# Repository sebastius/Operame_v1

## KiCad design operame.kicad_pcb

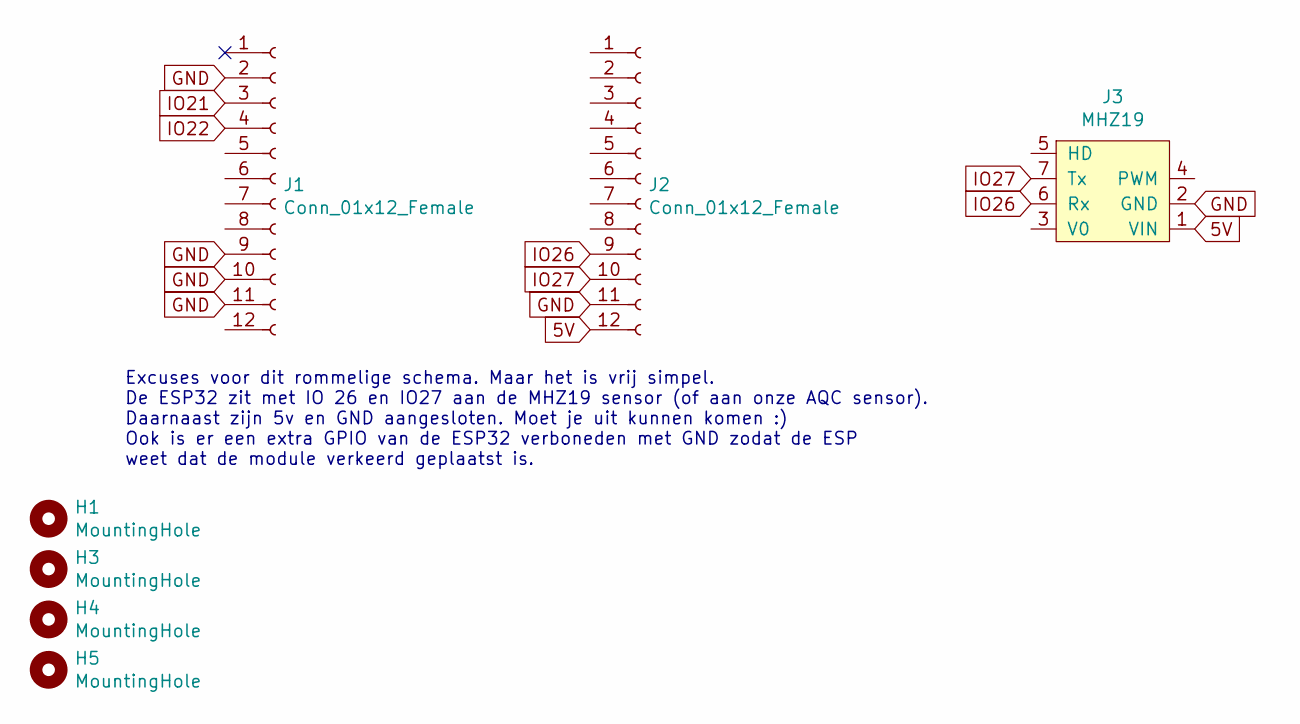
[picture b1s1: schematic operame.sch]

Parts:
H1, H3, H4, H5: MountingHole; MountingHole_3.2mm_M3
J1, J2: Conn_01x12_Female; PinSocket_1x12_P2.54mm_Vertical_SMD_Pin1Left
J3: MHZ19; Sensor_MH-Z19

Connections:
5V: J2.12, J3.1 (VIN)
GND: J1.2, J1.9, J1.10, J1.11, J2.11, J3.2 (GND)
IO21: J1.3
IO22: J1.4
IO26: J2.9, J3.6 (Rx)
IO27: J2.10, J3.7 (Tx)

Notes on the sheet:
Excuses voor dit rommelige schema. Maar het is vrij simpel. De ESP32 zit met IO 26 en IO27 aan de MHZ19 sensor (of aan onze AQC sensor). Daarnaast zijn 5v en GND aangesloten. Moet je uit kunnen komen :) Ook is er een extra GPIO van de ESP32 verboneden met GND zodat de ESP weet dat de module verkeer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

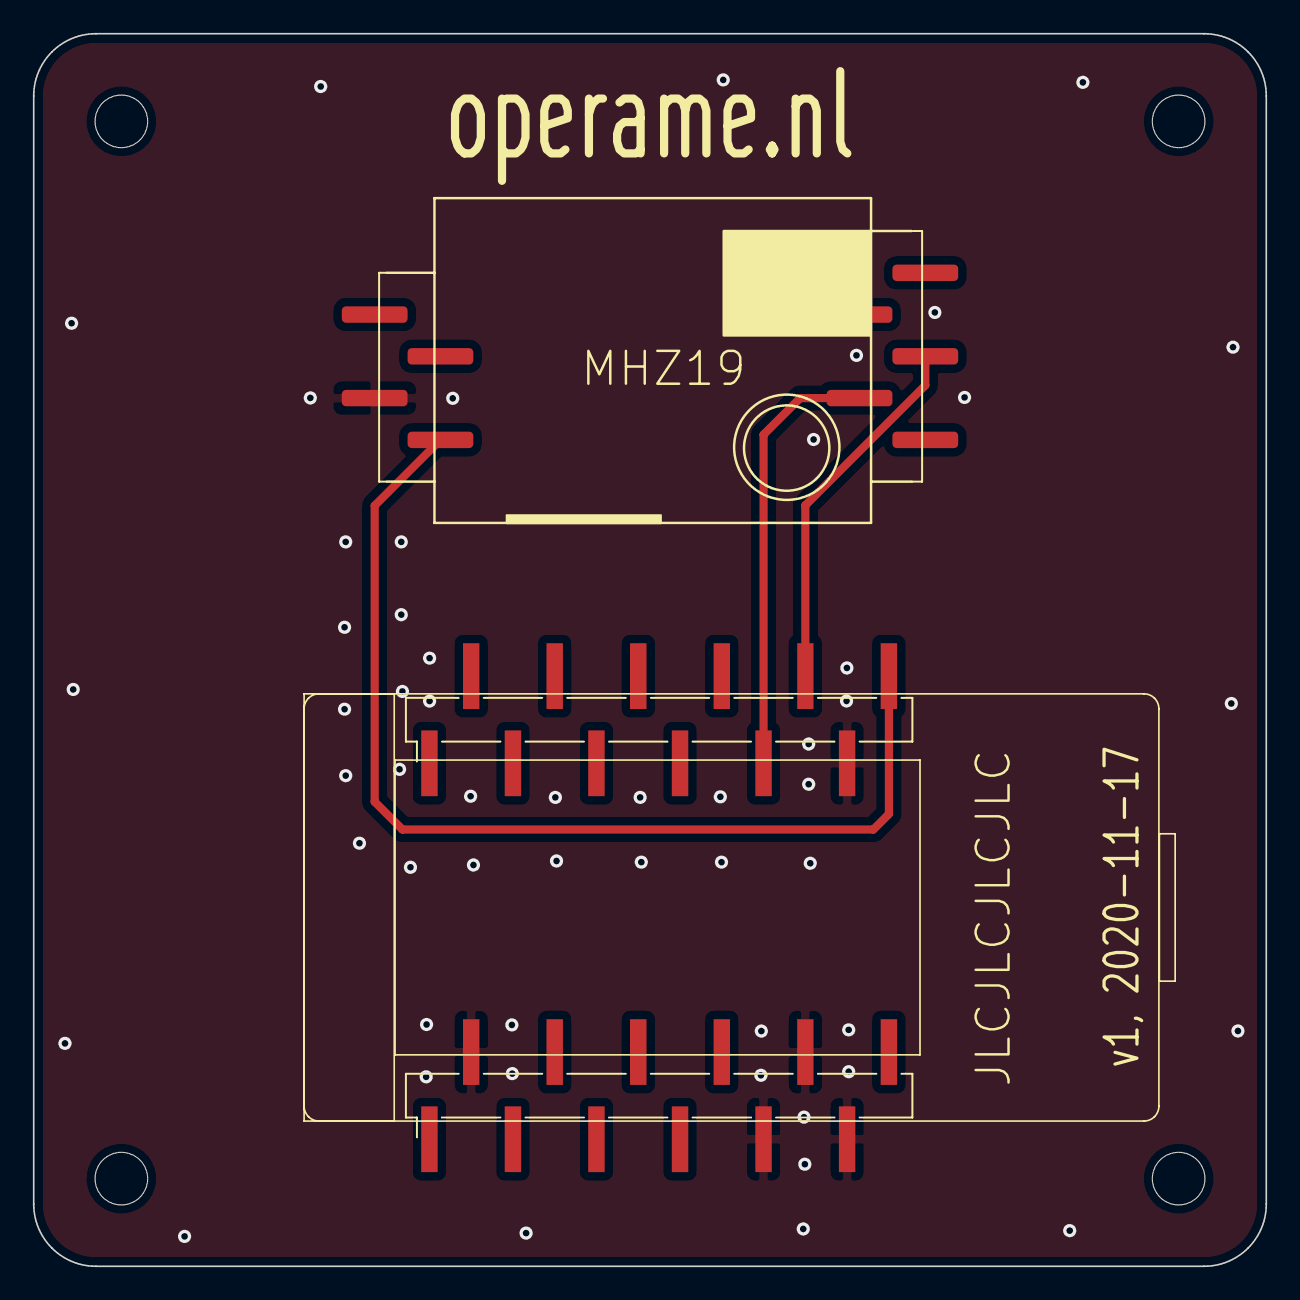
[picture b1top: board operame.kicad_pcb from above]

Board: 2 copper layers, 75.0 x 75.0 mm, 7 parts (0 on the bottom side), 4 nets.

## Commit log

2021-02-01 Add files via upload
    Its messy but it works.
